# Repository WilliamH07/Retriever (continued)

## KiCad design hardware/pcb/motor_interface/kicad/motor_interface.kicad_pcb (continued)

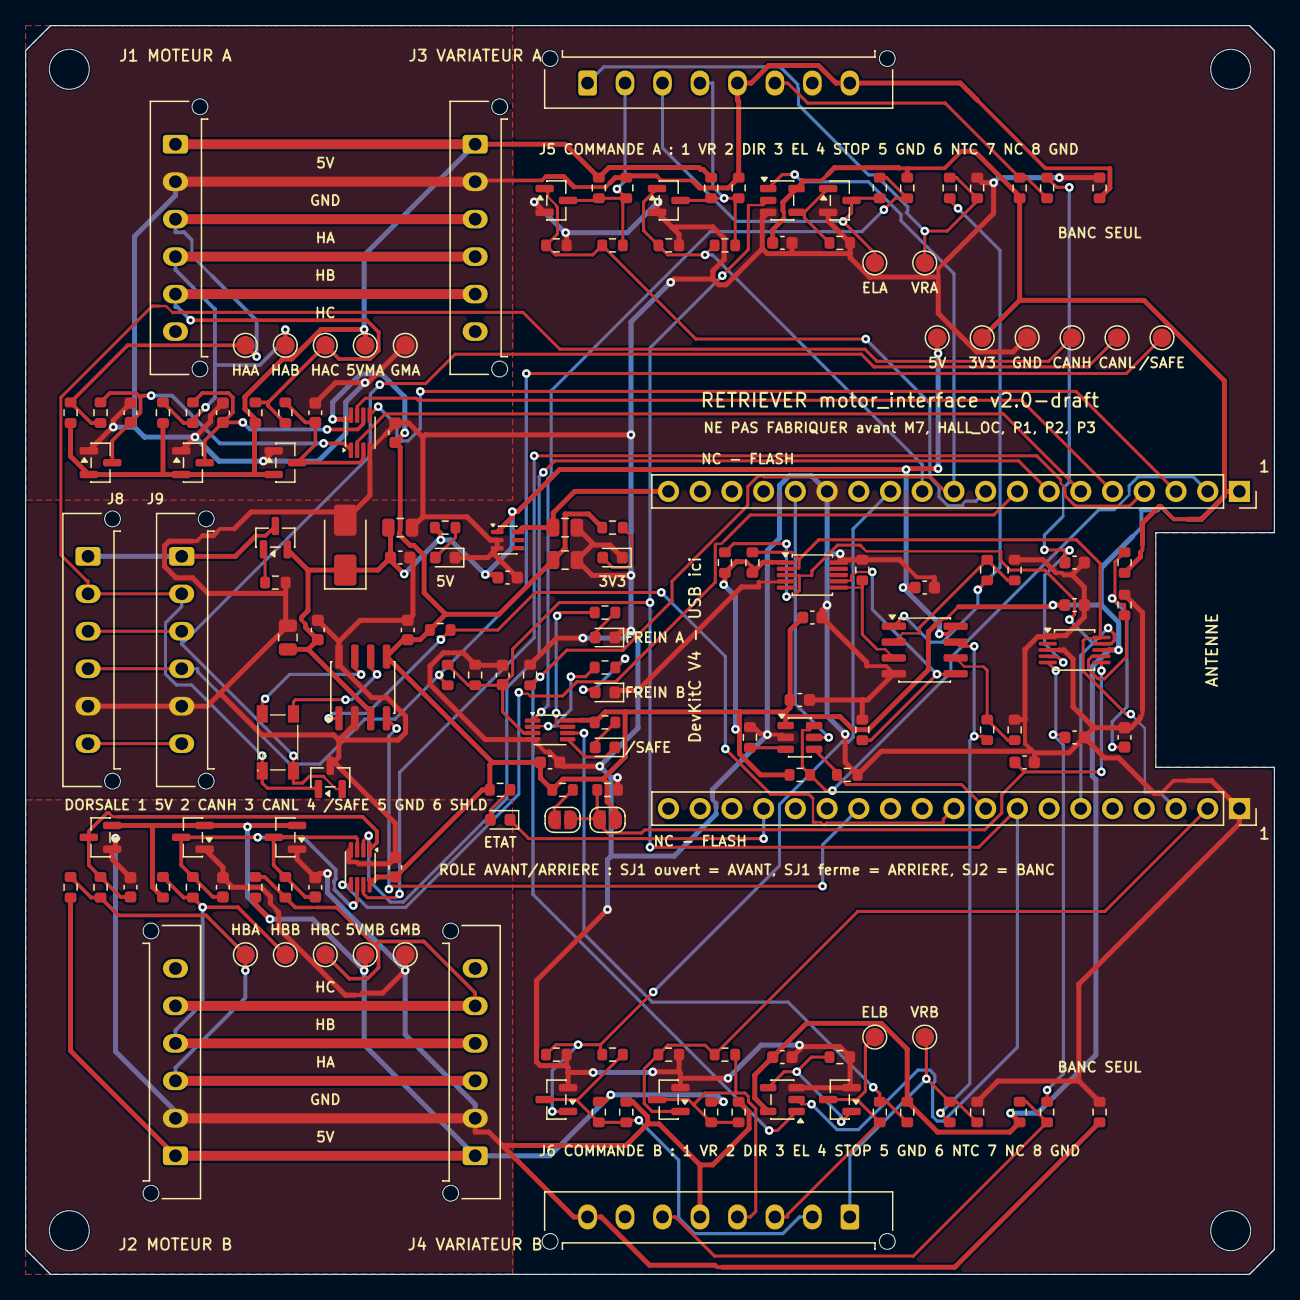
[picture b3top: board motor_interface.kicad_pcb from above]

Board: 4 copper layers, 100.0 x 100.0 mm, 167 parts (0 on the bottom side), 83 nets.

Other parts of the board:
H1, H2, H3, H4: M3; MountingHole_3.2mm_M3

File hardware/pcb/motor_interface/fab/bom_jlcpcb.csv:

Comment,Designator,Footprint,LCSC Part #
10uF,"C1,C4,C5",C_0805_2012Metric,C15850
100nF,"C10,C11,C113,C115,C12,C13,C14,C143,C145,C15,C16,C17,C18,C2,C7,C8",C_0603_1608Metric,C14663
10nF/100V,"C101,C105,C109,C151,C155,C159",C_0603_1608Metric,C43253
1uF,C3,C_0603_1608Metric,C15849
4.7uF,C6,C_0805_2012Metric,C1779
100pF,C9,C_0603_1608Metric,C14858
SMAJ6.0A,D1,D_SMA,C223993
BAT54S,"D101,D105,D109,D151,D155,D159",SOT-23,C47546
Everlight 19-217/GHC,"D2,D3",LED_0603_1608Metric,C72043
NUP2105L,D4,SOT-23,C14486
Hubei KENTO KT-0603R,"D5,D6,D7",LED_0603_1608Metric,C2286
ETAT,D8,LED_0603_1608Metric,C72041
Molex 43650-0615,"J1,J2,J3,J4,J8,J9",Molex_Micro-Fit_3.0_43650-0615_1x06_P3.00mm_Vertical,C505231
ACT45B-510,L1,IND-SMD_4P-L4.5-W3.2-TL,C76584
AO3401A,Q1,SOT-23,C15127
AO3400A,"Q101,Q106,Q111,Q131,Q136,Q141",SOT-23,C20917
10k,"R1,R14,R142,R145,R17,R172,R175,R20,R21,R22,R4",R_0603_1608Metric,C25804
100k,"R10,R131,R136,R141,R15,R161,R166,R171,R18,R7,R9",R_0603_1608Metric,C25803
2.2k,"R101,R102,R105,R106,R109,R110,R151,R152,R155,R156,R159,R160",R_0603_1608Metric,C4190
4.7k,"R11,R12",R_0603_1608Metric,C23162
15k,"R13,R16",R_0603_1608Metric,C22809
1M,"R143,R173,R6",R_0603_1608Metric,C22935
100Ω,"R144,R174",R_0603_1608Metric,C22775
3.3k,"R146,R176",R_0603_1608Metric,C22978
1k,"R147,R177,R2,R23,R24,R25,R26,R3",R_0603_1608Metric,C21190
20k,R19,R_0603_1608Metric,C4184
47k,R5,R_0603_1608Metric,C25819
6.8k,R8,R_0603_1608Metric,C23212
LM66100DCKR,U1,SOT-363_SC-70-6,C2869734
SN74LVC3G17DCUR,"U10,U11,U7",VSSOP-8_2.3x2mm_P0.5mm,C68245
SN74LVC1G08DBVR,"U12,U13",SOT-23-5,C7666
TCAN1042HVDR,U2,SOIC-8_3.9x4.9mm_P1.27mm,C127869
TPL5010DDCR,U3,SOT-23-6,C473912
MCP4728-E/UN,U4,MSOP-10_3x3mm_P0.5mm,C108207
TLV9062IDR,U5,SOIC-8_3.9x4.9mm_P1.27mm,C398355
ADS1115IDGSR,U6,TSSOP-10_3x3mm_P0.5mm,C37593

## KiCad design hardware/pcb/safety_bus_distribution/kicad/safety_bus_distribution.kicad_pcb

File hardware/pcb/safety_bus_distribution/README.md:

# Safety bus distribution board

> **v2.0 is designed** — schematic and layout generated, ERC and DRC clean,
> not yet fabricated. Every choice and its reason: [`decisions.md`](decisions.md)
> (French). Brief: [`cahier-des-charges.md`](cahier-des-charges.md).

| | |
|---|---|
| Size | 110 × 72 mm, 2 layers, 4 × M3 |
| Parts | 122 placed by the assembler, 9 Micro-Fit connectors through-hole |
| Per branch | eFuse `TPS259531` (≈0.95 A), ground PPTC 1.1 A / 48 V, CAN choke `ACT45B`, `NUP2105L` |
| Sources | [`kicad/`](kicad/) — KiCad 10 project, **generated** by [`scripts/build.py`](scripts/build.py) |
| Fabrication | [`fab/`](fab/) — Gerber zip, JLCPCB BOM and placement, schematic PDF, renders |

Rebuild everything: `./build.sh` then `./fab.sh` (needs the toolchain in
[`../outils.md`](../outils.md)). Do not edit the KiCad files by hand: change
`scripts/build.py` and rebuild, or the next build overwrites the change.

Carries the CAN bus and the `/SAFE` line to every node, and feeds each of them
5 V through its own protection. One trunk in, eight branches out.

**It has no microcontroller, and that is the point.** A board that sits on the
safety path and can crash, hang, or need reflashing is a liability. Everything
here is passive or analogue. There is nothing to debug at three in the morning.

It replaces the board previously called `can_distribution`. The rename is not
cosmetic: the `/SAFE` line runs to exactly the same four nodes as the CAN bus,
over exactly the same route. Pulling two looms side by side would have been
absurd.

## Why this board is built first

It is the only one of the three that no measurement blocks. `motor_interface`
waits on the Hall signal levels, `safety_power` waits on the BMS cut-off
threshold and the pack identity. This one waits on nothing.

Building it first puts three ESP32s on a working CAN bus on the bench within a
week, which is where the firmware, the frame protocol and `protocol.yaml` get
written — while the power measurements happen in parallel. That is the correct
use of the critical path.

## The trunk

Six conductors, one connector type, everywhere on the robot.

| Pin | Net | Wire |
|---|---|---|
| 1 | `5V_LOGIC` | orange |
| 2 | `CANH` | green |
| 3 | `CANL` | brown |
| 4 | `/SAFE` | violet |
| 5 | `GND_LOGIC` | black, white tracer |
| 6 | `SHIELD` | — |

Molex Micro-Fit 3.0, 6 circuits, 600 V, positive latch, 5.5 A per circuit at
20 AWG. Every node gets **two in parallel** so the bus passes through it without
a stub.

Violet is reserved for `/SAFE` itself. The e-stop loops and the brake command use
violet with a tracer — close enough to read as "safety" at a glance, distinct
enough that you cannot splice one into the other.

## Topology, stated plainly

A board with eight connectors *is* a star, and ISO 11898-2 asks for a line with
two terminations and short drops. At 500 kbit/s the bit time is 2 µs and a 30 cm
stub costs about 3 ns round trip, so a star works comfortably. That is not the
problem.

The problem is that if nobody writes it down, somebody eventually adds a three
metre drop. So the rule is on the silkscreen: **`STUB MAX 30 cm`**.

```
   Daisy chain — the normal case      Star — bench and fault-finding
   ┌───┐  ┌───┐  ┌───┐                     ┌──── trunk ────┐
   │IN │──│OUT│  │IN │── …                 │  │  │  │  │  │
   └───┘  └───┘  └───┘                    n1 n2 n3 n4 n5 n6
   120 Ω at the two physical ends      120 Ω on two branches only
```

## Termination you can verify

Split termination, always: 2 × 60 Ω with `CSPLIT` from the midpoint to ground.
It costs one capacitor and it cuts common-mode emission sharply. On a robot
where the CAN pair runs past four BLDC choppers, that is not a refinement.

Selectable by jumper at two positions, each with its own blue LED, so a glance
tells you how many are active.

And the acceptance test is printed on the board, because a termination jumper is
the classic thing nobody can account for six months later:

> **Bus unpowered, measure between `TP_CANH` and `TP_CANL`:**
> **60 Ω → correct.** 120 Ω → only one termination. 40 Ω → three.

Five seconds, no instrument beyond a multimeter.

## Per branch, and why each part is there

| Part | Against |
|---|---|
| `TCAN1042HVDR` at each node — not on this board | A power line touching `CANH`. See below |
| `NUP2105L` across CANH/CANL | ESD and **transients only** — see the caveat below. Clamps to 40 V at 5 A, where a `PESD1CAN` needs 70 V at 3 A |
| `ACT45B-510-2P-TL003` common mode choke | The 16–20 kHz chopping coupled from the phase wires. 200 mA rated, 1 Ω DCR |
| `1812L050/30` PPTC on the 5 V feed | One node shorting must not take down the other seven |
| **PPTC 500 mA in series with the branch ground** | The failure nobody plans for — see below |
| One green LED per branch | Knowing at a glance which node is actually powered |

### The transceiver choice belongs here even though the part sits elsewhere

The `SN65HVD230` in the original architecture is rated **−4 V to +16 V** on its
bus pins. This robot runs a 42 V rail in the same loom. A single contact between
a power conductor and `CANH` destroys **every transceiver on the bus at once** —
all four nodes, simultaneously.

The `TCAN1042HV` is rated **±70 V**. The same fault becomes survivable. It costs
a 5 V rail on each node instead of running natively at 3.3 V, and the `VIO` pin
handles the logic side. That is a good trade.

⚠️ **But do not oversell it.** The `NUP2105L` on every branch has a 24 V standoff
and breaks down between 26 and 32 V. A **sustained** 42 V contact makes it
conduct continuously and destroys it — on all eight branches — whatever the
transceiver is rated for. The TVS survives transients, not a permanent fault; it
fails short, which at least pulls the bus down visibly rather than letting the
fault propagate. The transceiver's ±70 V rating is what saves the *nodes*, and
the branch ground PPTC is what stops the fault current. Replacing eight TVS
diodes after a wiring mistake is the acceptable outcome here — not the same as
"nothing breaks".

Two things that will cost you an afternoon if you miss them: `STB` has an
internal pull-up, so **a floating `STB` pin silently puts the transceiver in
standby** — tie it to ground. And it is the `V` suffix, not the `H`, that brings
the `VIO` pin.

### The ground fuse

If a node's ground comes loose on the power side while the CAN cable stays
plugged in, that node's entire return current goes through a 0.5 mm² conductor
sized for a few tens of milliamps. It melts, or it heats and drags every ground
reference on the robot with it.

A 500 mA PPTC in series with each branch ground costs twenty cents and turns
that into a node that simply stops talking.

## `/SAFE`

Active low, open drain, wired-OR, referenced to **3.3 V** — not 5 V, so it lands
directly on an ESP32 pin with no level shifting.

**One** pull-up in the whole system: 1 kΩ to `3V3_HOTEL` on `safety_power`, **in
series with the mushroom's NC contact**. **One** pull-down, also on
`safety_power`: 10 kΩ. Every other board carries a 1 MΩ pull-down only, to define
its own state when it is unplugged from the trunk.

> A first draft of this board put a 10 kΩ pull-down on *every* board. With three
> boards that is 3.33 kΩ against a 4.7 kΩ pull-up: the high level lands at
> **2.07 V**, below the ESP32's 2.48 V VIH. The line would have read low
> permanently and the robot would never have released its brakes. One pull-up,
> one pull-down, and a level calculation written down — 3.3 × 10/(1+10) =
> **3.00 V**, 0.52 V of margin.

The mushroom's contact is **normally closed and in series with the pull-up**, not
across the line to ground. Released, the contact is closed, the pull-up is
connected, the line is high, the robot is permitted to run. Pressed — or the wire
cut, or the connector unplugged — the pull-up is disconnected and the pull-down
takes the line to ground. That is the only arrangement worth having, and it is
the opposite of what "NC contact pulls the line low" would suggest.

> ⚠️ **Read this before wiring `/SAFE` to the motor controllers.** Pulling
> `/SAFE` low does **not** brake the motors. On the ZS-X11H, `STOP` is active
> low and puts the drive into **coast**, and `BRAKE` is active **high**, so a
> released line releases the brake. The two-stage e-stop described in the
> architecture dossier assumes the opposite. The fix lives on
> `motor_interface` — a pull-up to 5 V sitting **on the loom, at the controller
> end**, which an open-drain MOSFET contradicts only while a hardware AND gate
> sees both `/SAFE` high and a live MCU. Lose any of them and `BRAKE` goes high.
> Putting the pull-up on the loom rather than the board is what makes unplugging
> the board brake rather than coast. See that board's specification.

## Node allocation

| Branch | Node |
|---|---|
| 1 | ESP32-SAFETY, on `safety_power` |
| 2 | ESP32-MOTION front |
| 3 | ESP32-MOTION rear |
| 4 | USB-CAN adapter to the X1 — `candleLight`/`gs_usb` firmware, not `slcan` |
| 5–7 | free — arm, turret, smart sensor, fifth wheel |
| 8 | bench |

Four nodes today, eight positions. The architecture brief asked for growth
without rewiring; this is what that looks like in copper.

## Bus load, for reference

675 frames per second at roughly 110 bits each, on 500 kbit/s, is about **15 %**
occupancy. There is a great deal of room.

## Bring up

Never plug a new board into the robot.

1. **Continuity.** Trunk pin *n* to branch pin *n*, eight branches, six pins.
   Then confirm no continuity between neighbours. Forty-eight measurements plus
   the shorts check.
2. **Terminations off, ohmmeter across `TP_CANH`/`TP_CANL`.** Expect open.
   Fit one jumper: 120 Ω. Fit the second: **60 Ω.**
3. **5 V alone** on the trunk, nothing else connected. Eight green LEDs.
   Current draw of a few milliamps. Above 50 mA, stop and find the short.
4. **`/SAFE` idle.** With the trunk pull-up present, every branch reads high.
   Short `/SAFE` to ground at any branch: every branch reads low. That is the
   wired-OR working.
5. **Two nodes, loopback.** Two ESP32s, 500 kbit/s, one sending, one receiving.
   Then unplug one mid-traffic and watch the other go bus-off and recover with
   `restart-ms 100`.
6. **Ground fuse.** Deliberately draw 1 A through a branch ground. The PPTC
   should trip. Better to learn this on the bench than in the field.

## Status

Specified. Nothing blocks it — no measurement, no pending decision. It is the
board to draw first.

Connector-by-connector pinout in [`hardware/icd.yaml`](../../icd.yaml).
Component justifications, with datasheet URLs, in
[`09-validation-composants.md`](../../../docs/architecture/09-validation-composants.md).

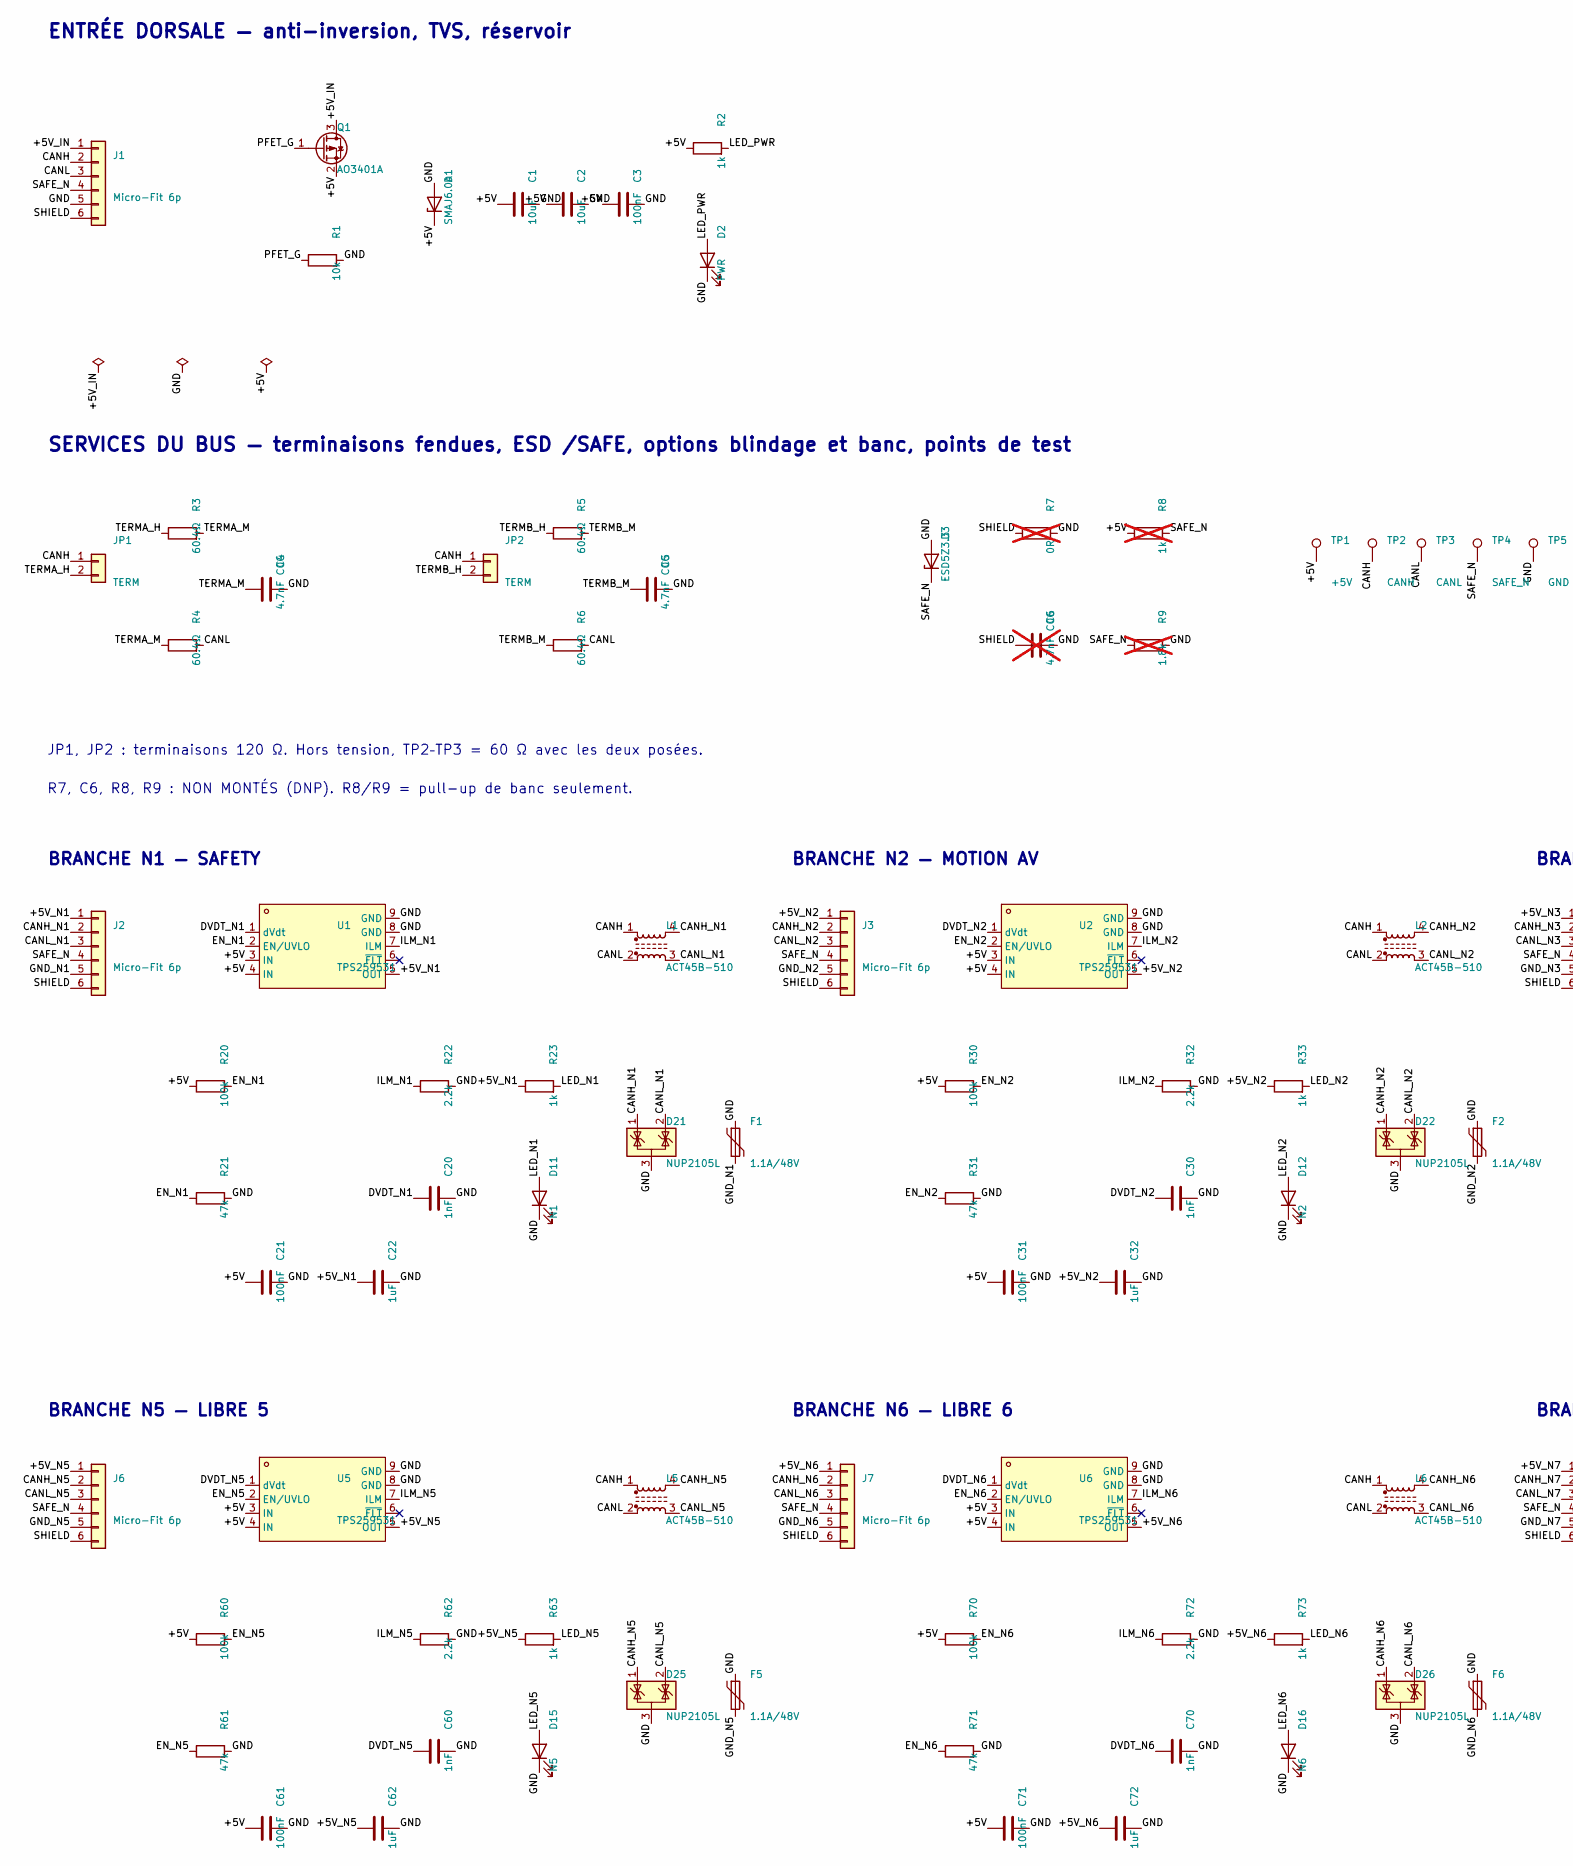
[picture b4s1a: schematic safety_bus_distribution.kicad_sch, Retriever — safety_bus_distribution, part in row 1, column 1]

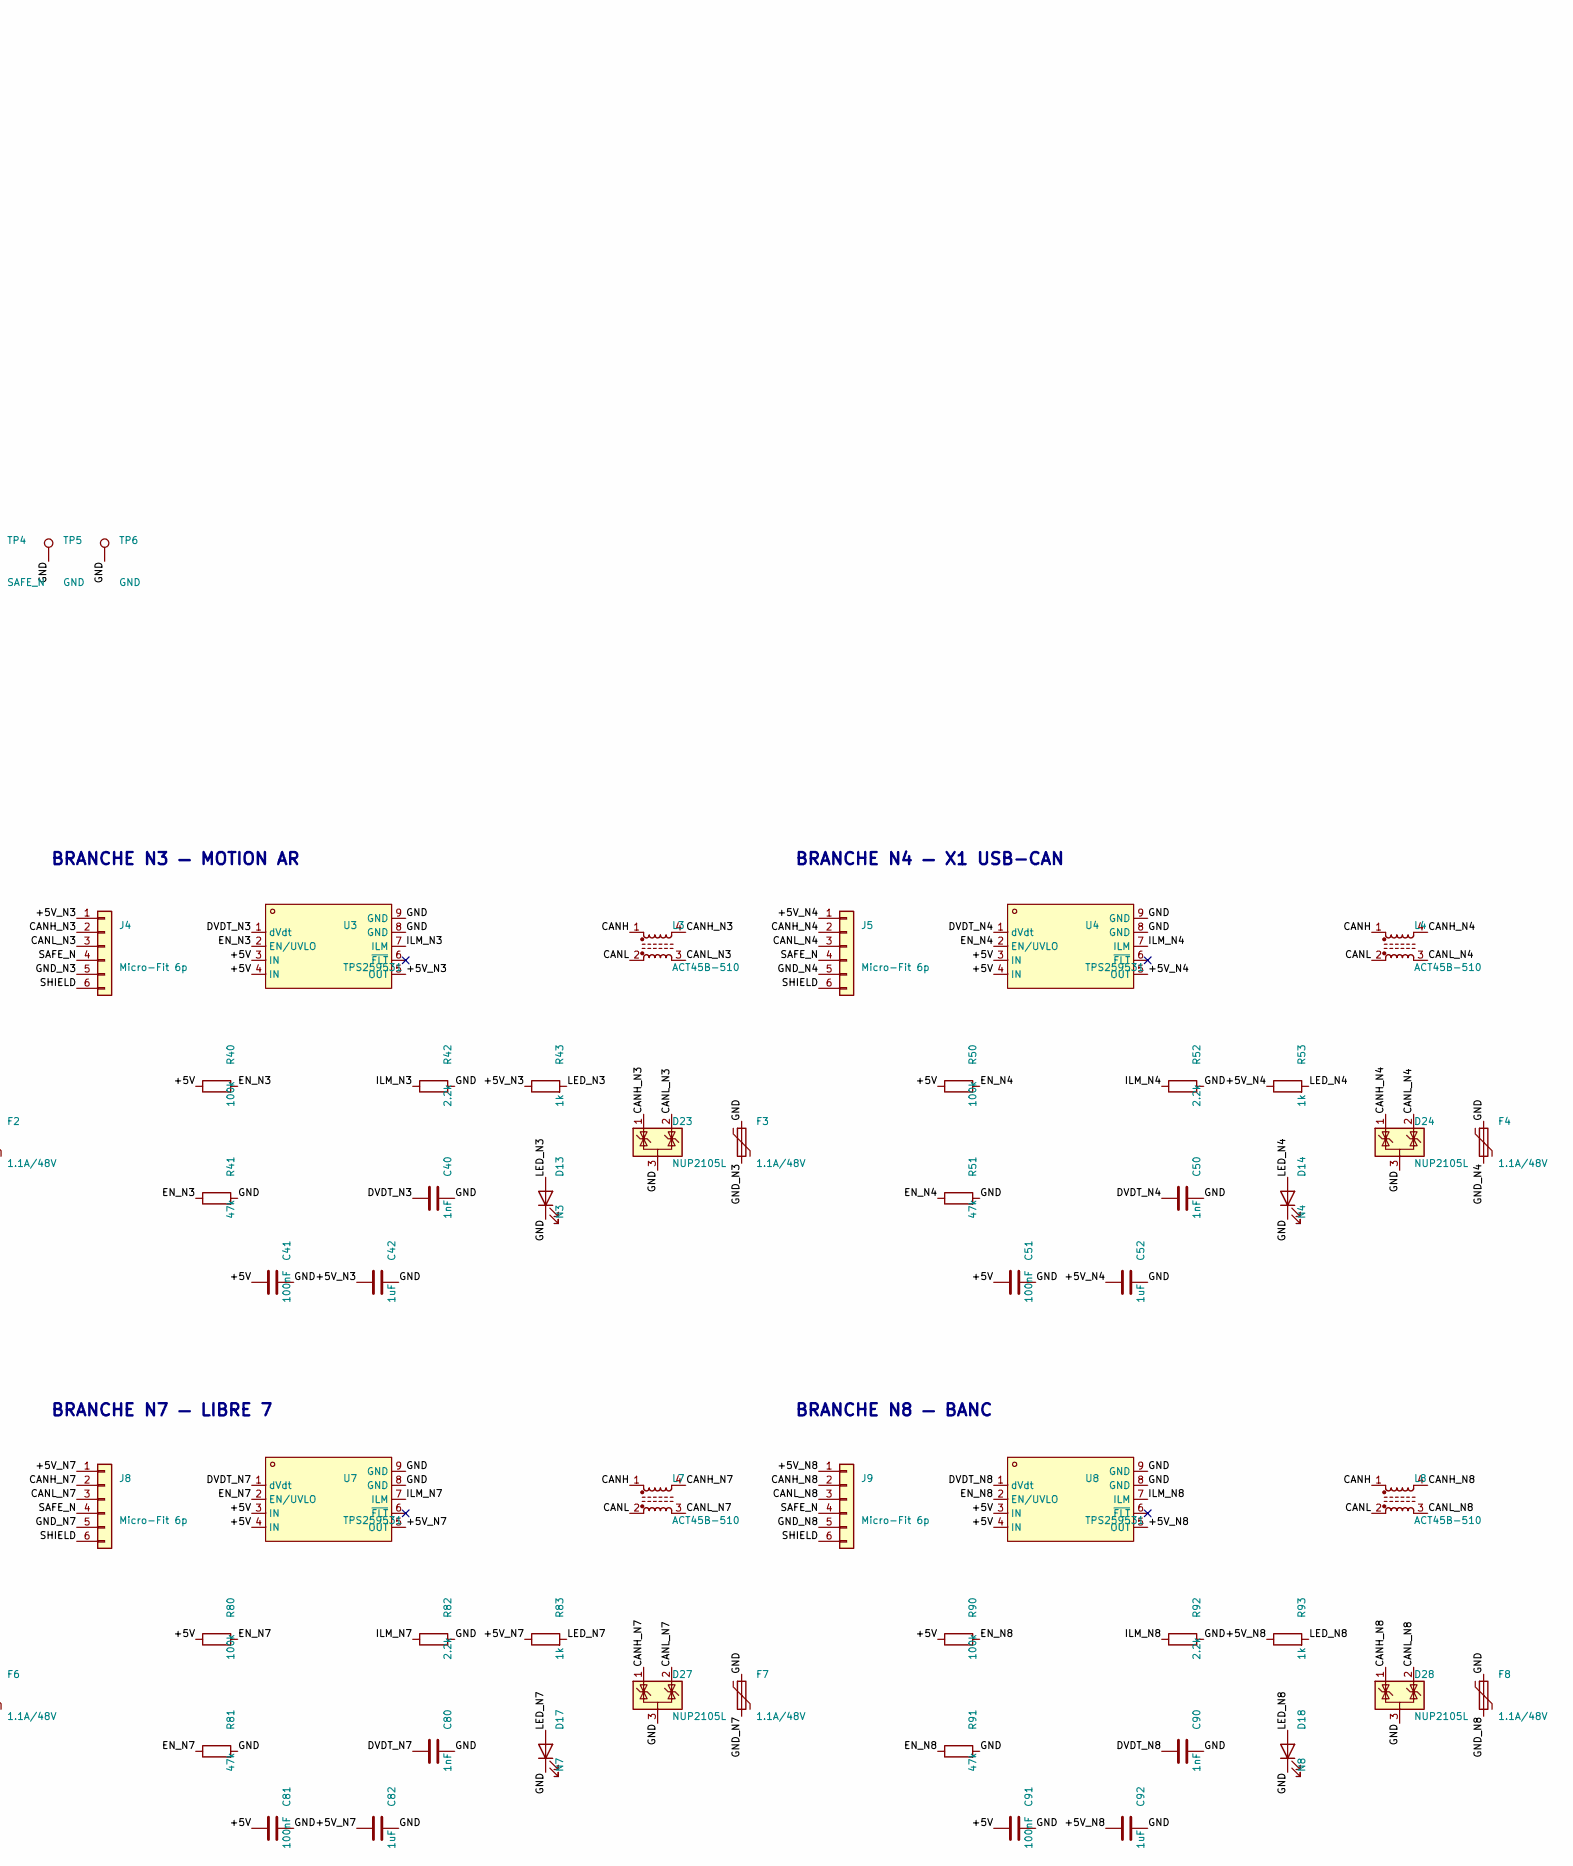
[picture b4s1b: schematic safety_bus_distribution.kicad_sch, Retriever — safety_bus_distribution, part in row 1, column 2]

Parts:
C1, C2: 10uF; C_0805_2012Metric; MPN CL21A106KAYNNNE; LCSC C15850
C3, C21, C31, C41, C51, C61, C71, C81, C91: 100nF; C_0603_1608Metric; MPN CC0603KRX7R9BB104; LCSC C14663
C4, C5: 4.7nF C0G; C_0603_1608Metric; MPN GRM1885C1H472JA01D; LCSC C85980
C6: 4.7nF C0G; C_0603_1608Metric; MPN GRM1885C1H472JA01D; LCSC C85980; not fitted
C20, C30, C40, C50, C60, C70, C80, C90: 1nF; C_0603_1608Metric; MPN 0603B102K500NT; LCSC C1588
C22, C32, C42, C52, C62, C72, C82, C92: 1uF; C_0603_1608Metric; MPN CL10A105KB8NNNC; LCSC C15849
D1: SMAJ6.0A; D_SMA; MPN Littelfuse SMAJ6.0A; LCSC C223993
D2: PWR; LED_0603_1608Metric; MPN Everlight 19-217/GHC; LCSC C72043
D3: ESD5Z3.3; D_SOD-523; MPN ESD5Z3.3T1G; LCSC C5252448
D11: N1; LED_0603_1608Metric; MPN Everlight 19-217/GHC; LCSC C72043
D12: N2; LED_0603_1608Metric; MPN Everlight 19-217/GHC; LCSC C72043
D13: N3; LED_0603_1608Metric; MPN Everlight 19-217/GHC; LCSC C72043
D14: N4; LED_0603_1608Metric; MPN Everlight 19-217/GHC; LCSC C72043
D15: N5; LED_0603_1608Metric; MPN Everlight 19-217/GHC; LCSC C72043
D16: N6; LED_0603_1608Metric; MPN Everlight 19-217/GHC; LCSC C72043
D17: N7; LED_0603_1608Metric; MPN Everlight 19-217/GHC; LCSC C72043
D18: N8; LED_0603_1608Metric; MPN Everlight 19-217/GHC; LCSC C72043
D21, D22, D23, D24, D25, D26, D27, D28: NUP2105L; SOT-23; MPN onsemi NUP2105LT1G; LCSC C14486
F1, F2, F3, F4, F5, F6, F7, F8: 1.1A/48V; F1812; MPN LUTE 1812L110/48QR; LCSC C19723490
J1, J2, J3, J4, J5, J6, J7, J8, J9: Micro-Fit 6p; Molex_Micro-Fit_3.0_43650-0615_1x06_P3.00mm_Vertical; MPN Molex 43650-0615; LCSC C505231
JP1, JP2: TERM; PinHeader_1x02_P2.54mm_Vertical; MPN 2.54 mm 1x2 header; LCSC C492401
L1, L2, L3, L4, L5, L6, L7, L8: ACT45B-510; IND-SMD_4P-L4.5-W3.2-TL; MPN TDK ACT45B-510-2P-TL003; LCSC C76584
Q1: AO3401A; SOT-23; MPN AOS AO3401A; LCSC C15127
R1: 10k; R_0603_1608Metric; MPN 0603WAF1002T5E; LCSC C25804
R2, R23, R33, R43, R53, R63, R73, R83, R93: 1k; R_0603_1608Metric; MPN 0603WAF1001T5E; LCSC C21190
R3, R4, R5, R6: 60.4Ω; R_0603_1608Metric; MPN RM06F60R4CT; LCSC C4099359
R7: 0R; R_0603_1608Metric; MPN 0603WAF0000T5E; LCSC C21189; not fitted
R8: 1k; R_0603_1608Metric; MPN 0603WAF1001T5E; LCSC C21190; not fitted
R9: 1.8k; R_0603_1608Metric; MPN 0603WAF1801T5E; LCSC C4177; not fitted
R20, R30, R40, R50, R60, R70, R80, R90: 100k; R_0603_1608Metric; MPN 0603WAF1003T5E; LCSC C25803
R21, R31, R41, R51, R61, R71, R81, R91: 47k; R_0603_1608Metric; MPN 0603WAF4702T5E; LCSC C25819
R22, R32, R42, R52, R62, R72, R82, R92: 2.2k; R_0603_1608Metric; MPN 0603WAF2201T5E; LCSC C4190
TP1: +5V; TestPoint_Pad_D1.5mm
TP2: CANH; TestPoint_Pad_D1.5mm
TP3: CANL; TestPoint_Pad_D1.5mm
TP4: SAFE_N; TestPoint_Pad_D1.5mm
TP5, TP6: GND; TestPoint_Pad_D1.5mm
U1, U2, U3, U4, U5, U6, U7, U8: TPS259531; Texas_DSG0008A_WSON-8-1EP_2x2mm_P0.5mm_EP0.9x1.6mm; MPN TI TPS259531DSGR; LCSC C2155674

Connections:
/+5V: C1.1, C2.1, C3.1, C21.1, C31.1, C41.1, C51.1, C61.1, C71.1, C81.1, C91.1, D1.1 (K), Q1.2 (S), R2.1, R8.1, R20.1, R30.1, R40.1, R50.1, R60.1, R70.1, R80.1, R90.1, TP1.1, U1.3 (IN), U1.4 (IN), U2.3 (IN), U2.4 (IN), U3.3 (IN), U3.4 (IN), U4.3 (IN), U4.4 (IN), U5.3 (IN), U5.4 (IN), U6.3 (IN), U6.4 (IN), U7.3 (IN), U7.4 (IN), U8.3 (IN), U8.4 (IN)
/+5V_IN: J1.1, Q1.3 (D)
/+5V_N1: C22.1, J2.1, R23.1, U1.5 (OUT)
/+5V_N2: C32.1, J3.1, R33.1, U2.5 (OUT)
/+5V_N3: C42.1, J4.1, R43.1, U3.5 (OUT)
/+5V_N4: C52.1, J5.1, R53.1, U4.5 (OUT)
/+5V_N5: C62.1, J6.1, R63.1, U5.5 (OUT)
/+5V_N6: C72.1, J7.1, R73.1, U6.5 (OUT)
/+5V_N7: C82.1, J8.1, R83.1, U7.5 (OUT)
/+5V_N8: C92.1, J9.1, R93.1, U8.5 (OUT)
/CANH: J1.2, JP1.1, JP2.1, L1.1, L2.1, L3.1, L4.1, L5.1, L6.1, L7.1, L8.1, TP2.1
/CANH_N1: D21.1 (K), J2.2, L1.4
/CANH_N2: D22.1 (K), J3.2, L2.4
/CANH_N3: D23.1 (K), J4.2, L3.4
/CANH_N4: D24.1 (K), J5.2, L4.4
/CANH_N5: D25.1 (K), J6.2, L5.4
/CANH_N6: D26.1 (K), J7.2, L6.4
/CANH_N7: D27.1 (K), J8.2, L7.4
/CANH_N8: D28.1 (K), J9.2, L8.4
/CANL: J1.3, L1.2, L2.2, L3.2, L4.2, L5.2, L6.2, L7.2, L8.2, R4.2, R6.2, TP3.1
/CANL_N1: D21.2 (K), J2.3, L1.3
/CANL_N2: D22.2 (K), J3.3, L2.3
/CANL_N3: D23.2 (K), J4.3, L3.3
/CANL_N4: D24.2 (K), J5.3, L4.3
/CANL_N5: D25.2 (K), J6.3, L5.3
/CANL_N6: D26.2 (K), J7.3, L6.3
/CANL_N7: D27.2 (K), J8.3, L7.3
/CANL_N8: D28.2 (K), J9.3, L8.3
/DVDT_N1: C20.1, U1.1 (dVdt)
/DVDT_N2: C30.1, U2.1 (dVdt)
/DVDT_N3: C40.1, U3.1 (dVdt)
/DVDT_N4: C50.1, U4.1 (dVdt)
/DVDT_N5: C60.1, U5.1 (dVdt)
/DVDT_N6: C70.1, U6.1 (dVdt)
/DVDT_N7: C80.1, U7.1 (dVdt)
/DVDT_N8: C90.1, U8.1 (dVdt)
/EN_N1: R20.2, R21.1, U1.2 (EN/UVLO)
/EN_N2: R30.2, R31.1, U2.2 (EN/UVLO)
/EN_N3: R40.2, R41.1, U3.2 (EN/UVLO)
/EN_N4: R50.2, R51.1, U4.2 (EN/UVLO)
/EN_N5: R60.2, R61.1, U5.2 (EN/UVLO)
/EN_N6: R70.2, R71.1, U6.2 (EN/UVLO)
/EN_N7: R80.2, R81.1, U7.2 (EN/UVLO)
/EN_N8: R90.2, R91.1, U8.2 (EN/UVLO)
/GND: C1.2, C2.2, C3.2, C4.2, C5.2, C6.2, C20.2, C21.2, C22.2, C30.2, C31.2, C32.2, C40.2, C41.2, C42.2, C50.2, C51.2, C52.2, C60.2, C61.2, C62.2, C70.2, C71.2, C72.2, C80.2, C81.2, C82.2, C90.2, C91.2, C92.2, D1.2 (A), D2.1 (K), D3.2 (A), D11.1 (K), D12.1 (K), D13.1 (K), D14.1 (K), D15.1 (K), D16.1 (K), D17.1 (K), D18.1 (K), D21.3 (A), D22.3 (A), D23.3 (A), D24.3 (A), D25.3 (A), D26.3 (A), D27.3 (A), D28.3 (A), F1.1, F2.1, F3.1, F4.1, F5.1, F6.1, F7.1, F8.1, J1.5, R1.2, R7.2, R9.2, R21.2, R22.2, R31.2, R32.2, R41.2, R42.2, R51.2, R52.2, R61.2, R62.2, R71.2, R72.2, R81.2, R82.2, R91.2, R92.2, TP5.1, TP6.1, U1.8 (GND), U1.9 (GND), U2.8 (GND), U2.9 (GND), U3.8 (GND), U3.9 (GND), U4.8 (GND), U4.9 (GND), U5.8 (GND), U5.9 (GND), U6.8 (GND), U6.9 (GND), U7.8 (GND), U7.9 (GND), U8.8 (GND), U8.9 (GND)
/GND_N1: F1.2, J2.5
/GND_N2: F2.2, J3.5
/GND_N3: F3.2, J4.5
/GND_N4: F4.2, J5.5
/GND_N5: F5.2, J6.5
/GND_N6: F6.2, J7.5
/GND_N7: F7.2, J8.5
/GND_N8: F8.2, J9.5
/ILM_N1: R22.1, U1.7 (ILM)
/ILM_N2: R32.1, U2.7 (ILM)
/ILM_N3: R42.1, U3.7 (ILM)
/ILM_N4: R52.1, U4.7 (ILM)
/ILM_N5: R62.1, U5.7 (ILM)
/ILM_N6: R72.1, U6.7 (ILM)
/ILM_N7: R82.1, U7.7 (ILM)
/ILM_N8: R92.1, U8.7 (ILM)
/LED_N1: D11.2 (A), R23.2
/LED_N2: D12.2 (A), R33.2
/LED_N3: D13.2 (A), R43.2
/LED_N4: D14.2 (A), R53.2
/LED_N5: D15.2 (A), R63.2
/LED_N6: D16.2 (A), R73.2
/LED_N7: D17.2 (A), R83.2
/LED_N8: D18.2 (A), R93.2
/LED_PWR: D2.2 (A), R2.2
/PFET_G: Q1.1 (G), R1.1
/SAFE_N: D3.1 (K), J1.4, J2.4, J3.4, J4.4, J5.4, J6.4, J7.4, J8.4, J9.4, R8.2, R9.1, TP4.1
/SHIELD: C6.1, J1.6, J2.6, J3.6, J4.6, J5.6, J6.6, J7.6, J8.6, J9.6, R7.1
/TERMA_H: JP1.2, R3.1
/TERMA_M: C4.1, R3.2, R4.1
/TERMB_H: JP2.2, R5.1
/TERMB_M: C5.1, R5.2, R6.1

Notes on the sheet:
ENTRÉE DORSALE — anti-inversion, TVS, réservoir
SERVICES DU BUS — terminaisons fendues, ESD /SAFE, options blindage et banc, points de test
JP1, JP2 : terminaisons 120 Ω. Hors tension, TP2–TP3 = 60 Ω avec les deux posées.
R7, C6, R8, R9 : NON MONTÉS (DNP). R8/R9 = pull-up de banc seulement.
BRANCHE N1 — SAFETY
BRANCHE N2 — MOTION AV
BRANCHE N3 — MOTION AR
BRANCHE N4 — X1 USB-CAN
BRANCHE N5 — LIBRE 5
BRANCHE N6 — LIBRE 6
BRANCHE N7 — LIBRE 7
BRANCHE N8 — BANC

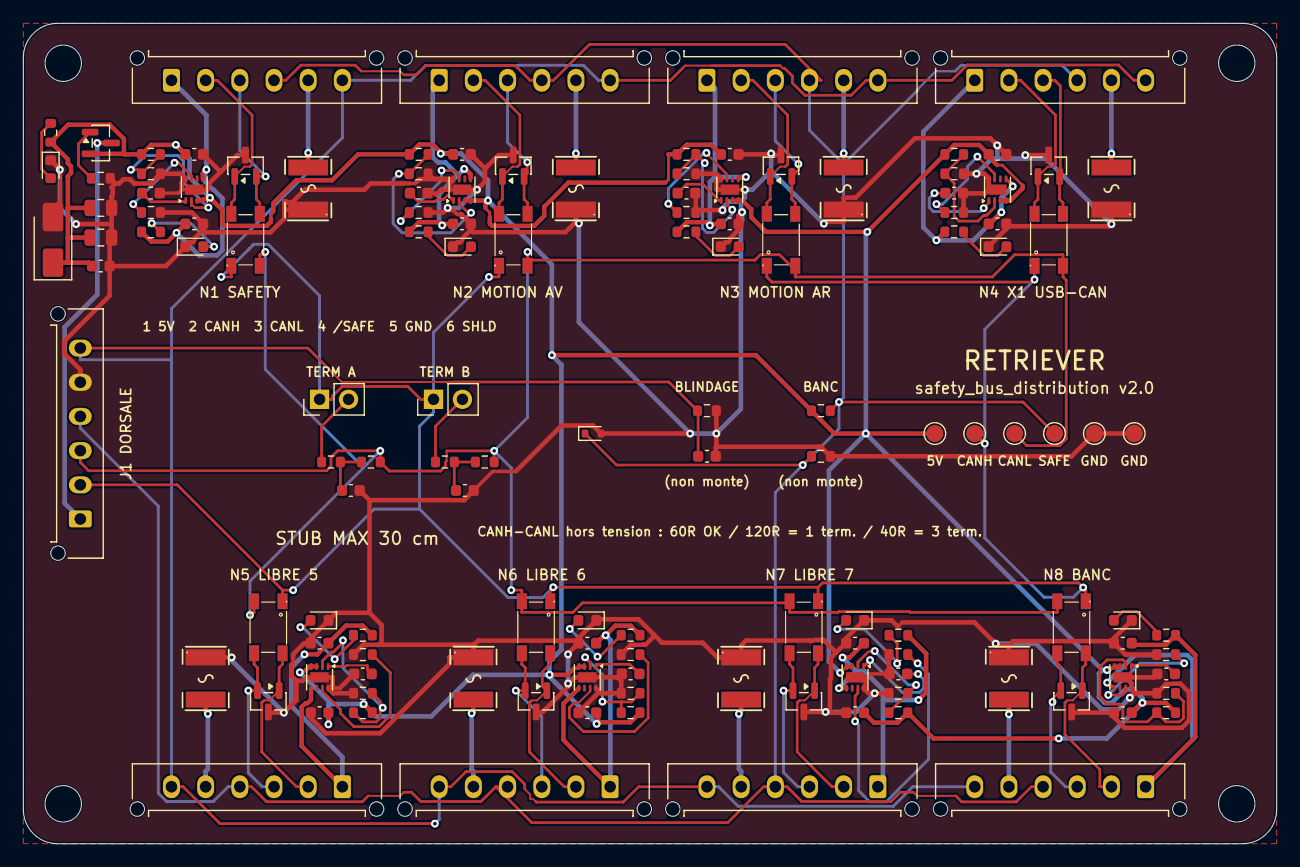
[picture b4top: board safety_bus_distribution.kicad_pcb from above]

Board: 2 copper layers, 110.0 x 72.0 mm, 136 parts (0 on the bottom side), 77 nets.

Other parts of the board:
H1, H2, H3, H4: M3; MountingHole_3.2mm_M3

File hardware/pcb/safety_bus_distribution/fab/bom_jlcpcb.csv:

Comment,Designator,Footprint,LCSC Part #
10uF,"C1,C2",C_0805_2012Metric,C15850
1nF,"C20,C30,C40,C50,C60,C70,C80,C90",C_0603_1608Metric,C1588
100nF,"C21,C3,C31,C41,C51,C61,C71,C81,C91",C_0603_1608Metric,C14663
1uF,"C22,C32,C42,C52,C62,C72,C82,C92",C_0603_1608Metric,C15849
4.7nF C0G,"C4,C5",C_0603_1608Metric,C85980
SMAJ6.0A,D1,D_SMA,C223993
Everlight 19-217/GHC,"D11,D12,D13,D14,D15,D16,D17,D18,D2",LED_0603_1608Metric,C72043
NUP2105L,"D21,D22,D23,D24,D25,D26,D27,D28",SOT-23,C14486
ESD5Z3.3,D3,D_SOD-523,C5252448
1.1A/48V,"F1,F2,F3,F4,F5,F6,F7,F8",F1812,C19723490
Micro-Fit 6p,"J1,J2,J3,J4,J5,J6,J7,J8,J9",Molex_Micro-Fit_3.0_43650-0615_1x06_P3.00mm_Vertical,C505231
TERM,"JP1,JP2",PinHeader_1x02_P2.54mm_Vertical,C492401
ACT45B-510,"L1,L2,L3,L4,L5,L6,L7,L8",IND-SMD_4P-L4.5-W3.2-TL,C76584
AO3401A,Q1,SOT-23,C15127
10k,R1,R_0603_1608Metric,C25804
1k,"R2,R23,R33,R43,R53,R63,R73,R83,R93",R_0603_1608Metric,C21190
100k,"R20,R30,R40,R50,R60,R70,R80,R90",R_0603_1608Metric,C25803
47k,"R21,R31,R41,R51,R61,R71,R81,R91",R_0603_1608Metric,C25819
2.2k,"R22,R32,R42,R52,R62,R72,R82,R92",R_0603_1608Metric,C4190
60.4Ω,"R3,R4,R5,R6",R_0603_1608Metric,C4099359
TPS259531,"U1,U2,U3,U4,U5,U6,U7,U8",Texas_DSG0008A_WSON-8-1EP_2x2mm_P0.5mm_EP0.9x1.6mm,C2155674

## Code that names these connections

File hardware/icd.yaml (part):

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
        precharge_fet:
          part: "P-canal 100 V SUD50P10-43L, 43 mOhm (S12)"
          driven_by: "ESP32-SAFETY directement (GPIO27 PRECH_EN), PAS par le TPS4810"
          why: >
            ⚠️ CONFLIT D'AFFECTATION. Dans la topologie TI, INP2/G2 pilote le FET
            de précharge et INP1 pilote Q1+Q2 ensemble. Dans la topologie de
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          4: {net: SPI_MISO, wire: vert}
          5: {net: SPI_MOSI, wire: bleu}
          6: {net: SPI_CS,   wire: gris}
          7: {net: IMU_INT,  wire: jaune_liseré,   note: "H_INTN, actif bas, GPIO à capacité de réveil"}
          8: {net: IMU_WAKE, wire: bleu, note: "PS0/WAKE — v1.3 : sortie P07 du TCA9555, tirée haut 10 kOhm (l'expander démarre en entrée, le pull-up tient PS0 haut) — S31"}
        v2_note: "33 Ohm série sur SCK, MOSI, CS et MISO ; IMU_INT sur GPIO36 (S31)"

      J18:
        name: FANS
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
    driven_low_by:
      - "ouverture du contact NF du champignon (déconnexion du pull-up)"
      - "drain ouvert de l'ESP32-SAFETY — MOSFET SAFE_HOLD (DMG1012T, grille GPIO32 tirée HAUT 10 kOhm : ESP32 absent, en reset ou en démarrage -> /SAFE bas) — S18"
      - "verrou 74LVC1G74 (DMG1012T sur Q barre) : remis à zéro par RSTn du TPL5010 ET par le comparateur ACS758 (OC_N), tient /SAFE bas jusqu'au front montant de SAFE_REARM (GPIO33) — D7, S16, S17, I8"
      - "ouverture du contact NF de l'e-stop radio (futur), en série lui aussi"

    consumed_by:
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      GPIO2: "NC — un pull-up externe empêcherait le download boot"

    assignments:
      GPIO5:  {net: CAN_TX,     note: "strapping, doit être HAUT au boot -> pull-up 10k vers 3V3"}
      GPIO4:  {net: CAN_RX,     note: "TCAN1042HV. STB DOIT ÊTRE TIRÉ À GND (pull-up interne = standby)"}
      GPIO21: {net: I2C_SDA,    note: "MCP4728 (0x60) + ADS1115 (0x48)"}
      GPIO22: {net: I2C_SCL,    note: ""}
      GPIO34: {net: HALL_A1,    note: "entrée seule — sortie push-pull du LVC3G17, aucun pull externe requis"}
      GPIO35: {net: HALL_B1,    note: "entrée seule"}
      GPIO36: {net: HALL_C1,    note: "entrée seule (SENSOR_VP)"}
      GPIO39: {net: HALL_A2,    note: "entrée seule (SENSOR_VN)"}
      GPIO32: {net: HALL_B2,    note: ""}
      GPIO33: {net: HALL_C2,    note: ""}
      GPIO25: {net: DIR_1,      note: "AO3400A drain ouvert (M19) — PAS de 2N7002, plus de DMG1012T"}
      GPIO14: {net: DIR_2,      note: ""}
      GPIO27: {net: STOP_1,     note: "commande seule, aucun rôle de sécurité"}
      GPIO23: {net: STOP_2,     note: "séparés par roue : permet de désactiver UNE roue en mode DEGRADED (§M.4)"}
      GPIO26: {net: BRAKE_RELEASE, note: "COMMUN AUX DEUX ROUES. Entrée des deux portes ET SN74LVC1G08 (une par roue, M21). Pull-down 100k obligatoire (R7)"}
      GPIO19: {net: SAFE_N_IN,  note: "interruption. Ligne référencée 3V3 ; 47 kOhm série, pull-down faible 1M local, 100 pF (M32)"}
      GPIO18: {net: WD_DONE,    note: "TPL5010 — reconnu sur transition BAS->HAUT, >= 20 ms avant le prochain WAKE. Pull-down 100 k sur DONE (M29)"}
      GPIO13: {net: WD_WAKE,    note: "TPL5010 — impulsion de 20 ms au début de chaque intervalle"}
      GPIO15: {net: LED_STATUS, note: "LED anode->3V3 via R, cathode->GPIO. Pull-up interne = LED éteinte au boot, log de boot préservé"}

    spare:
      GPIO16: {status: conditional, blocked_by: P3, note: "INUTILISABLE sur variante D0WDR2-V3 (PSRAM). Réserve conditionnelle"}
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      GPIO3_RX: "console — NC"

    assignments:
      GPIO5:  {net: CAN_TX,      dir: S,   default: "pull-up 10 k", note: "strapping : haut au boot"}
      GPIO34: {net: CAN_RX,      dir: E,   note: "entrée seule, TCAN1042HV push-pull"}
      GPIO21: {net: I2C_SDA,     dir: E/S, default: "2,2 k", note: "INA228 x5, ADS1115, TCA9555"}
      GPIO22: {net: I2C_SCL,     dir: S,   default: "2,2 k", note: "400 kHz"}
      GPIO18: {net: SPI_SCK,     dir: S,   note: "BNO085, 33 Ohm série"}
      GPIO23: {net: SPI_MOSI,    dir: S,   note: "33 Ohm"}
      GPIO19: {net: SPI_MISO,    dir: E,   note: "33 Ohm"}
      GPIO15: {net: SPI_CS,      dir: S,   default: "pull-up 10 k", note: "strapping MTDO : haut = log de boot conservé"}
      GPIO36: {net: IMU_INT,     dir: E,   default: "pull-up 10 k", note: "entrée seule, H_INTN actif bas"}
      GPIO25: {net: CTR_INP1,    dir: S,   default: "pull-down 100 k", note: "SÉCURITÉ : Q1"}
      GPIO26: {net: CTR_INP2,    dir: S,   default: "pull-down 100 k", note: "SÉCURITÉ : Q2"}
      GPIO27: {net: PRECH_EN,    dir: S,   default: "pull-down 100 k", note: "SÉCURITÉ : précharge"}
      GPIO32: {net: SAFE_HOLD,   dir: S,   default: "PULL-UP 10 k", note: "SÉCURITÉ : haut = /SAFE tenu bas"}
      GPIO33: {net: SAFE_REARM,  dir: S,   default: "pull-down 100 k", note: "SÉCURITÉ : front montant = réarmement du verrou"}
      GPIO39: {net: SAFE_N_IN,   dir: E,   default: "1 kOhm série", note: "lecture de /SAFE, entrée seule"}
      GPIO14: {net: WD_DONE,     dir: S,   default: "pull-down 100 k", note: "TPL5010 ; une impulsion parasite au boot ne fait qu'un DONE de plus"}
      GPIO35: {net: BMS_RX,      dir: E,   note: "entrée seule, via ADuM1201"}
      GPIO17: {net: BMS_TX,      dir: S,   note: "⚠️ P3"}
      GPIO4:  {net: FAN_PWM,     dir: S,   default: "pull-down 100 k", note: "25 kHz, MOSFET drain ouvert"}
      GPIO2:  {net: LED_DATA_F,  dir: S,   default: "pull-down 100 k", note: "strapping : doit rester bas, aucun pull-up"}
      GPIO13: {net: LED_DATA_R,  dir: S,   default: "pull-down 100 k"}
      GPIO16: {net: GPIO16_1W,   status: conditional, blocked_by: P3, note: "réserve conditionnelle : option DS18B20 (R159 non monté)"}

    spare:
      note: >
        GPIO16 seulement si P3 confirme un ESP32-D0WD-V3 sans PSRAM ; GPIO0 contraint.
        SI P3 RÉVÈLE UNE VARIANTE PSRAM, GPIO16 et GPIO17 sont perdus : BMS_TX passe
        sur GPIO13 et les deux bandeaux LED se partagent GPIO2 (même motif à l'avant
        et à l'arrière). Un expander SPI ou un second TCA9555 en v2.1 le lèverait.

    expander_tca9555:
      address: "0x20"
      boot_state: "entrée partout au démarrage : aucune sortie active avant configuration logicielle"
      P00: {net: WD_WAKE,     dir: E, note: "sortie WAKE du TPL5010 ; scrutée, le DONE part de GPIO14"}
      P01: {net: TPS_FLT_N,   dir: E, note: "défaut du contrôleur (pull-up 10 k)"}
      P02: {net: SCP_TEST,    dir: S, note: "auto-test du comparateur SCP (pull-down 100 k)"}
      P03: {net: LATCH_Q,     dir: E, note: "état du verrou watchdog (1 = armé)"}
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    blocks: [motor_interface, safety_power]
  P3:
    what: "Variante exacte du module : D0WD-V3 ou D0WDR2-V3 (PSRAM) ?"
    why: "Sur la variante PSRAM, GPIO16 et GPIO17 sont inutilisables. v1.3 : motor_interface les garde en réserve ; safety_power y met BMS_TX (GPIO17) et l'option DS18B20 (GPIO16), avec un repli prévu dans gpio_allocation.safety_power"
    blocks: [motor_interface, safety_power]
  M4:
    what: "Polarité réelle de EL/BRAKE et STOP sur TES cartes"
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
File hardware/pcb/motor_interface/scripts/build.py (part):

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P_OPA = ("Amplifier_Operational:TLV9062xD", "Package_SO:SOIC-8_3.9x4.9mm_P1.27mm", "TLV9062IDR", "C398355",
         "TI TLV9062IDR")
P_CAN = ("Interface_CAN_LIN:TJA1042T-3", "Package_SO:SOIC-8_3.9x4.9mm_P1.27mm", "TCAN1042HVDR", "C127869",
         "TI TCAN1042HVDR")   # pin-compatible symbol: TXD GND VCC RXD VIO CANL CANH STB
P_CMC = ("Filter:Choke_CommonMode_FerriteCore_1423", "lcsc:IND-SMD_4P-L4.5-W3.2-TL",
         "ACT45B-510", "C76584", "TDK ACT45B-510-2P-TL003")
P_CANESD = ("Power_Protection:NUP2105L", "Package_TO_SOT_SMD:SOT-23", "NUP2105L", "C14486", "onsemi NUP2105LT1G")
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          "7": None,            # GND in the user guide, unlabeled in the schematic: left open (P2)
          "8": "SAFE_N_IN", "9": "WD_DONE", "10": "CAN_TX",
          "11": None, "12": None,                 # IO17/IO16: reserve, PSRAM variant (P3)
          "13": "CAN_RX", "14": None, "15": None,  # IO0/IO2 strapping: NC
          "16": "LED_STATUS", "17": None, "18": None, "19": None}
    c.add("J10", P_SOCK, j2, pcb=(MOD_PIN1_X, MOD_ROW_TOP), rot=270, value="DevKitC J2 (3V3…5V)", size=(60, 60))
    c.add("J11", P_SOCK, j3, pcb=(MOD_PIN1_X, MOD_ROW_BOT), rot=270, value="DevKitC J3 (GND…CLK)", size=(60, 60))
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    c.block("CAN — TCAN1042HVDR, STB à la masse, VIO 3,3 V, pas de terminaison sur cette carte", 30, 200, 260)
    c.add("U2", P_CAN, {"1": "CAN_TX", "2": "GND", "3": "+5V", "4": "CAN_RX", "5": "+3V3", "6": "CANL_T",
                        "7": "CANH_T", "8": "GND"}, pcb=(27.0, 53.0), rot=90)
    c.R("R4", "10k", "+3V3", "CAN_TX", pcb=(33.2, 48.4), rot=0)     # GPIO5 strapping: high at boot
    c.C("C6", "4.7u", "+5V", "GND", pcb=(21.0, 49.0), rot=90)
    c.C("C7", "100n", "+5V", "GND", pcb=(23.4, 48.4), rot=90)
    c.C("C8", "100n", "+3V3", "GND", pcb=(30.6, 48.4), rot=90)
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          pcb=(62.0, 57.0), rot=0)
    # TPL5010 SNAS651A table 3: 6.788 kΩ -> 2 s. 6.8 kΩ 1 % gives ~2.0 s.
    c.R("R8", "6.8k", "WD_DELAY", "GND", pcb=(58.0, 57.0), rot=90)
    c.R("R9", "100k", "WD_DONE", "GND", pcb=(65.8, 60.0), rot=0)   # no DONE edge while GPIO18 floats
    c.R("R10", "100k", "+3V3", "ESP_EN", pcb=(62.0, 60.0), rot=0)    # RSTn open drain: TI recommends 100k
    c.C("C10", "100n", "+3V3", "GND", pcb=(62.0, 54.0), rot=0)

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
